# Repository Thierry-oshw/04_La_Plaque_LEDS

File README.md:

# 04_La_Plaque_LEDS

La_Plaque_LEDS est constituée de 64 leds RGB WS2812B, toutes en série, constituant une "matrice" de 8 * 8 leds.

Ces LEDS sont plus connues comme "NEOPIXELS". Les bibliothèques logicielles, comme celle d'Adafruit par exemple, permettent de les piloter facilement.

La licence est celle du CERN Open Hardware Licence version 2; CERN-OHL-P ; permissive.
Le fichier de cette license est présent dans le répertoire: cern_ohl_p_v2.txt

## Photos

Ci-joint la photo de la version de 2020_12_06 // Here picture of version 2020_12_06:

## Connection et fonctionnement

Ci-joint le schéma du connecteur du module de la version de 2020_12_06

Le module fonctionne de la façon suivante:
Il faut l'alimenter avec une tension comprise entre 3.7V et 5.3V sur la pin +5V. Une tension comme celle de l'USB classique convient parfaitement. (Ne pas oublier GND bien sûr).

La pin S0 permet de communiquer avec la première LED, en attaquant la pin "Din" de la LED.

La pin back0 permet de récupérer le signal sortant "Dout" de la LED.

[Plus d'informations sur le site de Worldsemi](http://www.world-semi.com/ "http://www.world-semi.com")

Les LEDS sont réparties de la façon suivante:

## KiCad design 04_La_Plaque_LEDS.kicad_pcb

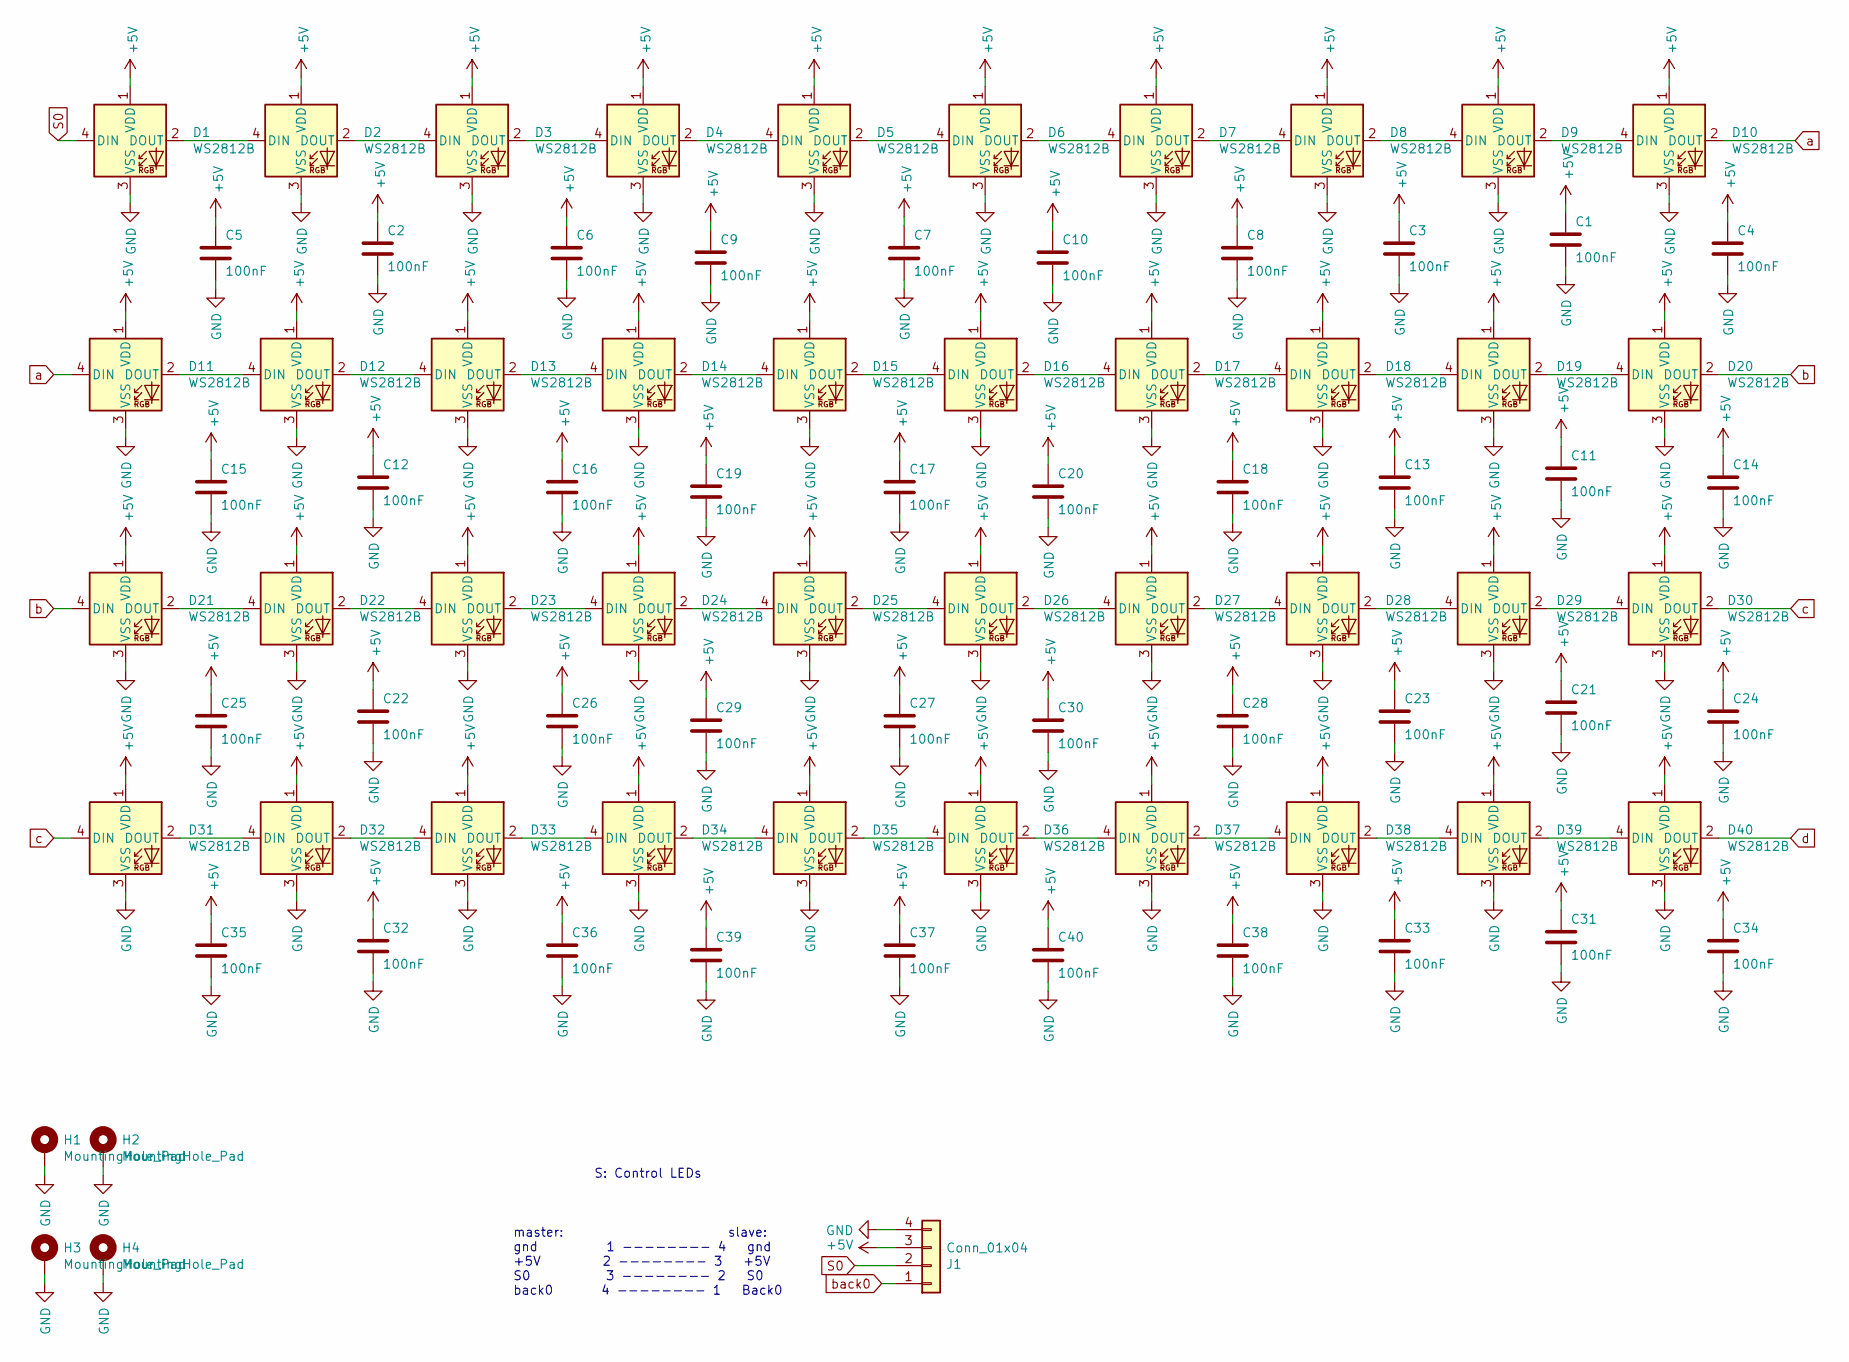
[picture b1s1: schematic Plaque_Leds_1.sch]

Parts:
C1, C2, C3, C4, C5, C6, C7, C8, C9, C10, C11, C12, C13, C14, C15, C16, C17, C18, C19, C20, C21, C22, C23, C24, C25, C26, C27, C28, C29, C30, C31, C32, C33, C34, C35, C36, C37, C38, C39, C40: 100nF; C_0603_1608Metric
D1, D2, D3, D4, D5, D6, D7, D8, D9, D10, D11, D12, D13, D14, D15, D16, D17, D18, D19, D20, D21, D22, D23, D24, D25, D26, D27, D28, D29, D30, D31, D32, D33, D34, D35, D36, D37, D38, D39, D40: WS2812B; LED_WS2812B_PLCC4_5.0x5.0mm_P3.2mm
H1, H2, H3, H4: MountingHole_Pad; MountingHole_3.2mm_M3_Pad_Via
J1: Conn_01x04; JST_XH_S4B-XH-A_1x04_P2.50mm_Horizontal

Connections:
+5V: C1.1, C2.1, C3.1, C4.1, C5.1, C6.1, C7.1, C8.1, C9.1, C10.1, C11.1, C12.1, C13.1, C14.1, C15.1, C16.1, C17.1, C18.1, C19.1, C20.1, C21.1, C22.1, C23.1, C24.1, C25.1, C26.1, C27.1, C28.1, C29.1, C30.1, C31.1, C32.1, C33.1, C34.1, C35.1, C36.1, C37.1, C38.1, C39.1, C40.1, D1.1 (VDD), D2.1 (VDD), D3.1 (VDD), D4.1 (VDD), D5.1 (VDD), D6.1 (VDD), D7.1 (VDD), D8.1 (VDD), D9.1 (VDD), D10.1 (VDD), D11.1 (VDD), D12.1 (VDD), D13.1 (VDD), D14.1 (VDD), D15.1 (VDD), D16.1 (VDD), D17.1 (VDD), D18.1 (VDD), D19.1 (VDD), D20.1 (VDD), D21.1 (VDD), D22.1 (VDD), D23.1 (VDD), D24.1 (VDD), D25.1 (VDD), D26.1 (VDD), D27.1 (VDD), D28.1 (VDD), D29.1 (VDD), D30.1 (VDD), D31.1 (VDD), D32.1 (VDD), D33.1 (VDD), D34.1 (VDD), D35.1 (VDD), D36.1 (VDD), D37.1 (VDD), D38.1 (VDD), D39.1 (VDD), D40.1 (VDD), J1.3; also elsewhere on the board
GND: C1.2, C2.2, C3.2, C4.2, C5.2, C6.2, C7.2, C8.2, C9.2, C10.2, C11.2, C12.2, C13.2, C14.2, C15.2, C16.2, C17.2, C18.2, C19.2, C20.2, C21.2, C22.2, C23.2, C24.2, C25.2, C26.2, C27.2, C28.2, C29.2, C30.2, C31.2, C32.2, C33.2, C34.2, C35.2, C36.2, C37.2, C38.2, C39.2, C40.2, D1.3 (VSS), D2.3 (VSS), D3.3 (VSS), D4.3 (VSS), D5.3 (VSS), D6.3 (VSS), D7.3 (VSS), D8.3 (VSS), D9.3 (VSS), D10.3 (VSS), D11.3 (VSS), D12.3 (VSS), D13.3 (VSS), D14.3 (VSS), D15.3 (VSS), D16.3 (VSS), D17.3 (VSS), D18.3 (VSS), D19.3 (VSS), D20.3 (VSS), D21.3 (VSS), D22.3 (VSS), D23.3 (VSS), D24.3 (VSS), D25.3 (VSS), D26.3 (VSS), D27.3 (VSS), D28.3 (VSS), D29.3 (VSS), D30.3 (VSS), D31.3 (VSS), D32.3 (VSS), D33.3 (VSS), D34.3 (VSS), D35.3 (VSS), D36.3 (VSS), D37.3 (VSS), D38.3 (VSS), D39.3 (VSS), D40.3 (VSS), H1.1, H2.1, H3.1, H4.1, J1.4; also elsewhere on the board
unnamed: D1.2 (DOUT), D2.4 (DIN)
unnamed: D2.2 (DOUT), D3.4 (DIN)
unnamed: D3.2 (DOUT), D4.4 (DIN)
unnamed: D4.2 (DOUT), D5.4 (DIN)
unnamed: D5.2 (DOUT), D6.4 (DIN)
unnamed: D6.2 (DOUT), D7.4 (DIN)
unnamed: D7.2 (DOUT), D8.4 (DIN)
unnamed: D8.2 (DOUT), D9.4 (DIN)
unnamed: D9.2 (DOUT), D10.4 (DIN)
unnamed: D11.2 (DOUT), D12.4 (DIN)
unnamed: D12.2 (DOUT), D13.4 (DIN)
unnamed: D13.2 (DOUT), D14.4 (DIN)
unnamed: D14.2 (DOUT), D15.4 (DIN)
unnamed: D15.2 (DOUT), D16.4 (DIN)
unnamed: D16.2 (DOUT), D17.4 (DIN)
unnamed: D17.2 (DOUT), D18.4 (DIN)
unnamed: D18.2 (DOUT), D19.4 (DIN)
unnamed: D19.2 (DOUT), D20.4 (DIN)
unnamed: D21.2 (DOUT), D22.4 (DIN)
unnamed: D22.2 (DOUT), D23.4 (DIN)
unnamed: D23.2 (DOUT), D24.4 (DIN)
unnamed: D24.2 (DOUT), D25.4 (DIN)
unnamed: D25.2 (DOUT), D26.4 (DIN)
unnamed: D26.2 (DOUT), D27.4 (DIN)
unnamed: D27.2 (DOUT), D28.4 (DIN)
unnamed: D28.2 (DOUT), D29.4 (DIN)
unnamed: D29.2 (DOUT), D30.4 (DIN)
unnamed: D31.2 (DOUT), D32.4 (DIN)
unnamed: D32.2 (DOUT), D33.4 (DIN)
unnamed: D33.2 (DOUT), D34.4 (DIN)
unnamed: D34.2 (DOUT), D35.4 (DIN)
unnamed: D35.2 (DOUT), D36.4 (DIN)
unnamed: D36.2 (DOUT), D37.4 (DIN)
unnamed: D37.2 (DOUT), D38.4 (DIN)
unnamed: D38.2 (DOUT), D39.4 (DIN)
unnamed: D39.2 (DOUT), D40.4 (DIN)
S0: D1.4 (DIN), J1.2
a: D10.2 (DOUT), D11.4 (DIN)
b: D20.2 (DOUT), D21.4 (DIN)
back0: J1.1; also elsewhere on the board
c: D30.2 (DOUT), D31.4 (DIN)
d: D40.2 (DOUT); also elsewhere on the board

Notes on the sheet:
S: Control LEDs
master: slave: gnd 1 -------- 4 gnd +5V 2 -------- 3 +5V S0 3 -------- 2 S0 back0 4 -------- 1 Back0

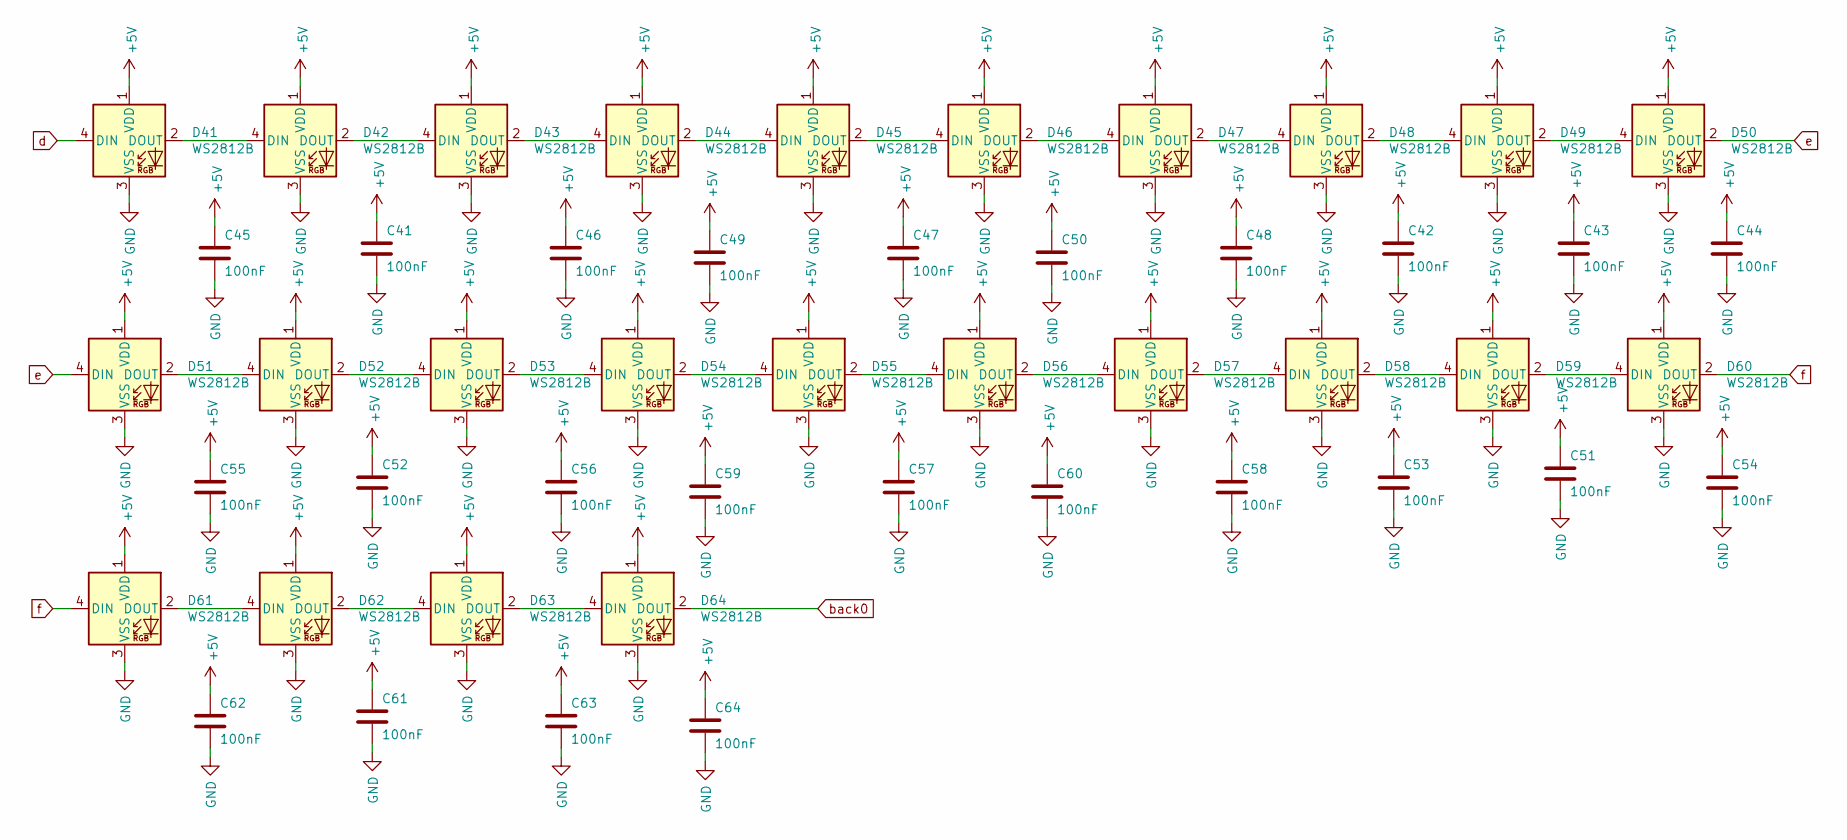
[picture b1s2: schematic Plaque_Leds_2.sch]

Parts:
C41, C42, C43, C44, C45, C46, C47, C48, C49, C50, C51, C52, C53, C54, C55, C56, C57, C58, C59, C60, C61, C62, C63, C64: 100nF; C_0603_1608Metric
D41, D42, D43, D44, D45, D46, D47, D48, D49, D50, D51, D52, D53, D54, D55, D56, D57, D58, D59, D60, D61, D62, D63, D64: WS2812B; LED_WS2812B_PLCC4_5.0x5.0mm_P3.2mm

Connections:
+5V: C41.1, C42.1, C43.1, C44.1, C45.1, C46.1, C47.1, C48.1, C49.1, C50.1, C51.1, C52.1, C53.1, C54.1, C55.1, C56.1, C57.1, C58.1, C59.1, C60.1, C61.1, C62.1, C63.1, C64.1, D41.1 (VDD), D42.1 (VDD), D43.1 (VDD), D44.1 (VDD), D45.1 (VDD), D46.1 (VDD), D47.1 (VDD), D48.1 (VDD), D49.1 (VDD), D50.1 (VDD), D51.1 (VDD), D52.1 (VDD), D53.1 (VDD), D54.1 (VDD), D55.1 (VDD), D56.1 (VDD), D57.1 (VDD), D58.1 (VDD), D59.1 (VDD), D60.1 (VDD), D61.1 (VDD), D62.1 (VDD), D63.1 (VDD), D64.1 (VDD); also elsewhere on the board
GND: C41.2, C42.2, C43.2, C44.2, C45.2, C46.2, C47.2, C48.2, C49.2, C50.2, C51.2, C52.2, C53.2, C54.2, C55.2, C56.2, C57.2, C58.2, C59.2, C60.2, C61.2, C62.2, C63.2, C64.2, D41.3 (VSS), D42.3 (VSS), D43.3 (VSS), D44.3 (VSS), D45.3 (VSS), D46.3 (VSS), D47.3 (VSS), D48.3 (VSS), D49.3 (VSS), D50.3 (VSS), D51.3 (VSS), D52.3 (VSS), D53.3 (VSS), D54.3 (VSS), D55.3 (VSS), D56.3 (VSS), D57.3 (VSS), D58.3 (VSS), D59.3 (VSS), D60.3 (VSS), D61.3 (VSS), D62.3 (VSS), D63.3 (VSS), D64.3 (VSS); also elsewhere on the board
unnamed: D41.2 (DOUT), D42.4 (DIN)
unnamed: D42.2 (DOUT), D43.4 (DIN)
unnamed: D43.2 (DOUT), D44.4 (DIN)
unnamed: D44.2 (DOUT), D45.4 (DIN)
unnamed: D45.2 (DOUT), D46.4 (DIN)
unnamed: D46.2 (DOUT), D47.4 (DIN)
unnamed: D47.2 (DOUT), D48.4 (DIN)
unnamed: D48.2 (DOUT), D49.4 (DIN)
unnamed: D49.2 (DOUT), D50.4 (DIN)
unnamed: D51.2 (DOUT), D52.4 (DIN)
unnamed: D52.2 (DOUT), D53.4 (DIN)
unnamed: D53.2 (DOUT), D54.4 (DIN)
unnamed: D54.2 (DOUT), D55.4 (DIN)
unnamed: D55.2 (DOUT), D56.4 (DIN)
unnamed: D56.2 (DOUT), D57.4 (DIN)
unnamed: D57.2 (DOUT), D58.4 (DIN)
unnamed: D58.2 (DOUT), D59.4 (DIN)
unnamed: D59.2 (DOUT), D60.4 (DIN)
unnamed: D61.2 (DOUT), D62.4 (DIN)
unnamed: D62.2 (DOUT), D63.4 (DIN)
unnamed: D63.2 (DOUT), D64.4 (DIN)
back0: D64.2 (DOUT); also elsewhere on the board
d: D41.4 (DIN); also elsewhere on the board
e: D50.2 (DOUT), D51.4 (DIN)
f: D60.2 (DOUT), D61.4 (DIN)

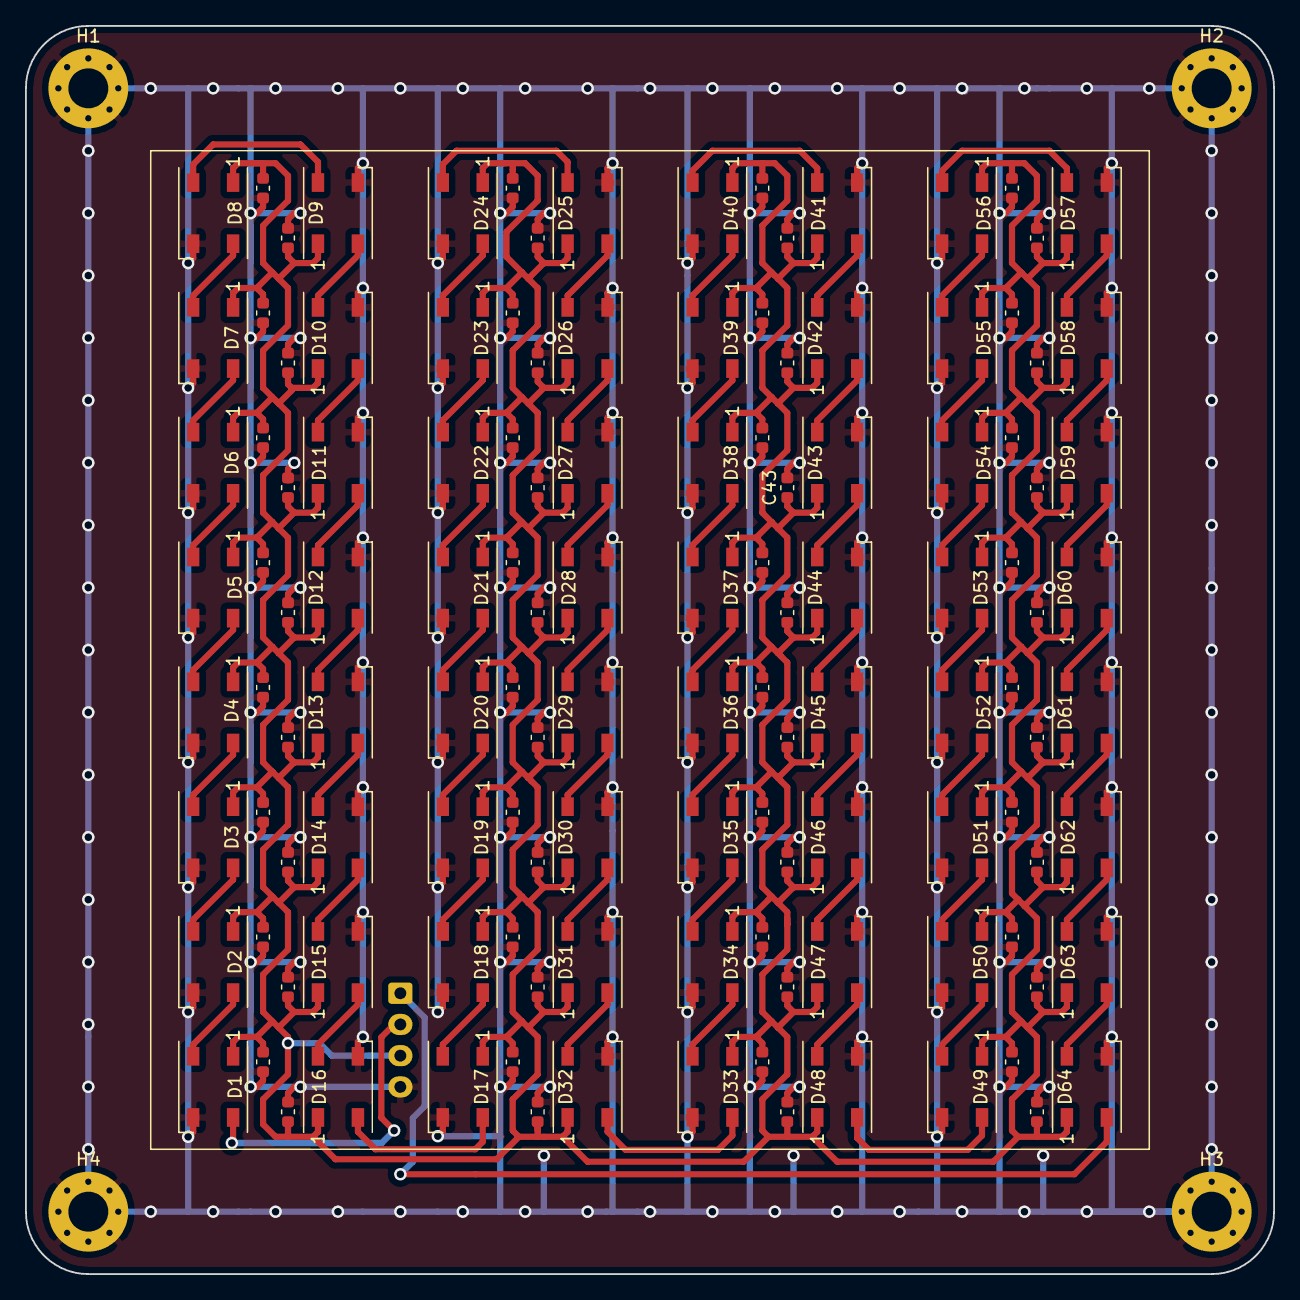
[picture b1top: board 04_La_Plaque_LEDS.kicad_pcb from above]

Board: 2 copper layers, 100.0 x 100.0 mm, 133 parts (1 on the bottom side), 67 nets.

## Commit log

2020-12-05 jst coudé
2020-12-05 génération fichiers fabrication
2020-12-06 tourné connecteur + silks
2021-07-24 maj split librairies
2021-09-07 MAJ README
    ajout description du module
2023-05-02 chgt nom fichier licence
